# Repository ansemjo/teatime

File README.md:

# Readme

## Notes on the question of voltage regulation

* There's only two components that are somewhat relevant in terms of voltage:
  * the ATtiny; handles 1.7–5.5V per datasheet
  * the LCD; wants 3V per datasheet
* Many of the similar LCD modules are advertised as 3.0–5V compatible.
  * [GoodDisplay's own precautions say that overvoltage will (merely) "shorten its life"](https://www.good-display.com/news/102.html)
  * [Another explainer says that overvoltage usually (only) results in ghosting](https://focuslcds.com/journals/lcd-voltage-inputs-for-lcd-displays-explained/)
* I'll have a diode behind the battery to prevent charging the coin cell in any case.
* The LCD is driven directly by the ATtiny IO pins, so *if* I want to regulate ... I'll need to regulate the input voltage to the ATtiny.
* The ATtiny pins can only handle about VDD + 0.5V, so I'll need either:
  * "Simple" protection with input resistors to limit the current; per § 34.2 of the datasheet it is acceptable to limit the current with $R = \frac{(V_{pin} - (VDD + 0.6))}{I_{Cn}}$, where $I_{Cn} = 1 \text{mA}$
    * How does this interact with the pull-up requirement on I2C pins?
  * "Full" level shifting for any logic pins, i.e. external I2C connectors and programming ports; except UPDI can handle up to 13V regardless of VDD

* Another funky solution would be to omit the regulation and "just" stay within the ATtiny's limits. Then implement the "own voltage" sensing (which is usually used for battery voltage detection; aside: how does that work behind a diode?) to check what voltage is applied on startup. If it's more than 3.3V, use PWM modulation on the IO pins to the display to keep the average at around 3V?

## Driving the LCD

* Aha! These LCDs are so cheap because they don't include and driver electronics. And it's actually not that trivial to drive.
* You *can* apply a constant voltage but that will destroy the LCD over time through ... elctrophoresis? Either way, you need to apply AC by alternating the polarity of each segment during each frame.
* *Do* drive the commons and segments that you *don't* want to be visible, but drive them with equal voltages during both halves of the frame to keep differential at zero. But you still do need to alternate the voltage.
* There's a nice [application note by Atmel: AVR241](https://ww1.microchip.com/downloads/en/AppNotes/doc2569.pdf).
* And [an article by Pacific Display Devices](https://www.pacificdisplay.com/lcd_multiplex_drive.htm).
* And particularly useful is an [application note by ST Microelectronics: AN1447](https://www.st.com/resource/en/application_note/an1447-software-driver-for-4multiplexed-lcd-with-a-standard-st62-stmicroelectronics.pdf). It actually describes how to drive a 4-multiplexed LCD with a simple microcontroller.

## Notes on Components

### The LCD

* Ain't nobody got space for that many pins! I *really* didn't want to use a 40-pin component. Especially because I don't have any microcontrollers that have enough IO ports.
* The 12 pin variant requires time multiplexing but I'm kinda used to that from the other two display projects I built already.

### 32.768 kHz Crystal

* I [picked a crystal from the same series](https://uk.farnell.com/abracon/abs07-120-32-768khz-t/crystal-32-768khz-6pf-3-2-x-1/dp/2467864) that David Johnson-Davies used; but a (to me) more common 12.5 pF loading capacitor value.

* [Per an Electronics StackExchange post](https://electronics.stackexchange.com/questions/39103/selecting-loading-capacitor-values-for-32-khz-crystal), the formula to select (two identical) loading capacitors $C$ is $C_{load} = \frac{C}{2} + C_{parasitic}$, where the parasitic capacitance of the PCB is usually assumed to be around 2.5 pF. Rearranging for the "unknown" yields $C = 2\cdot(C_{load} - C_{parasitic})$ and with $C_{load} = 12.5\,pF$ this gives $C \approx 20\,pF$.
* I chose to use 0603 capacitors because this is a new part in my personal stock, I feel very confident soldering smaller parts than 0805 by now and I'll probably only ever use these capacitors in this exact combination.

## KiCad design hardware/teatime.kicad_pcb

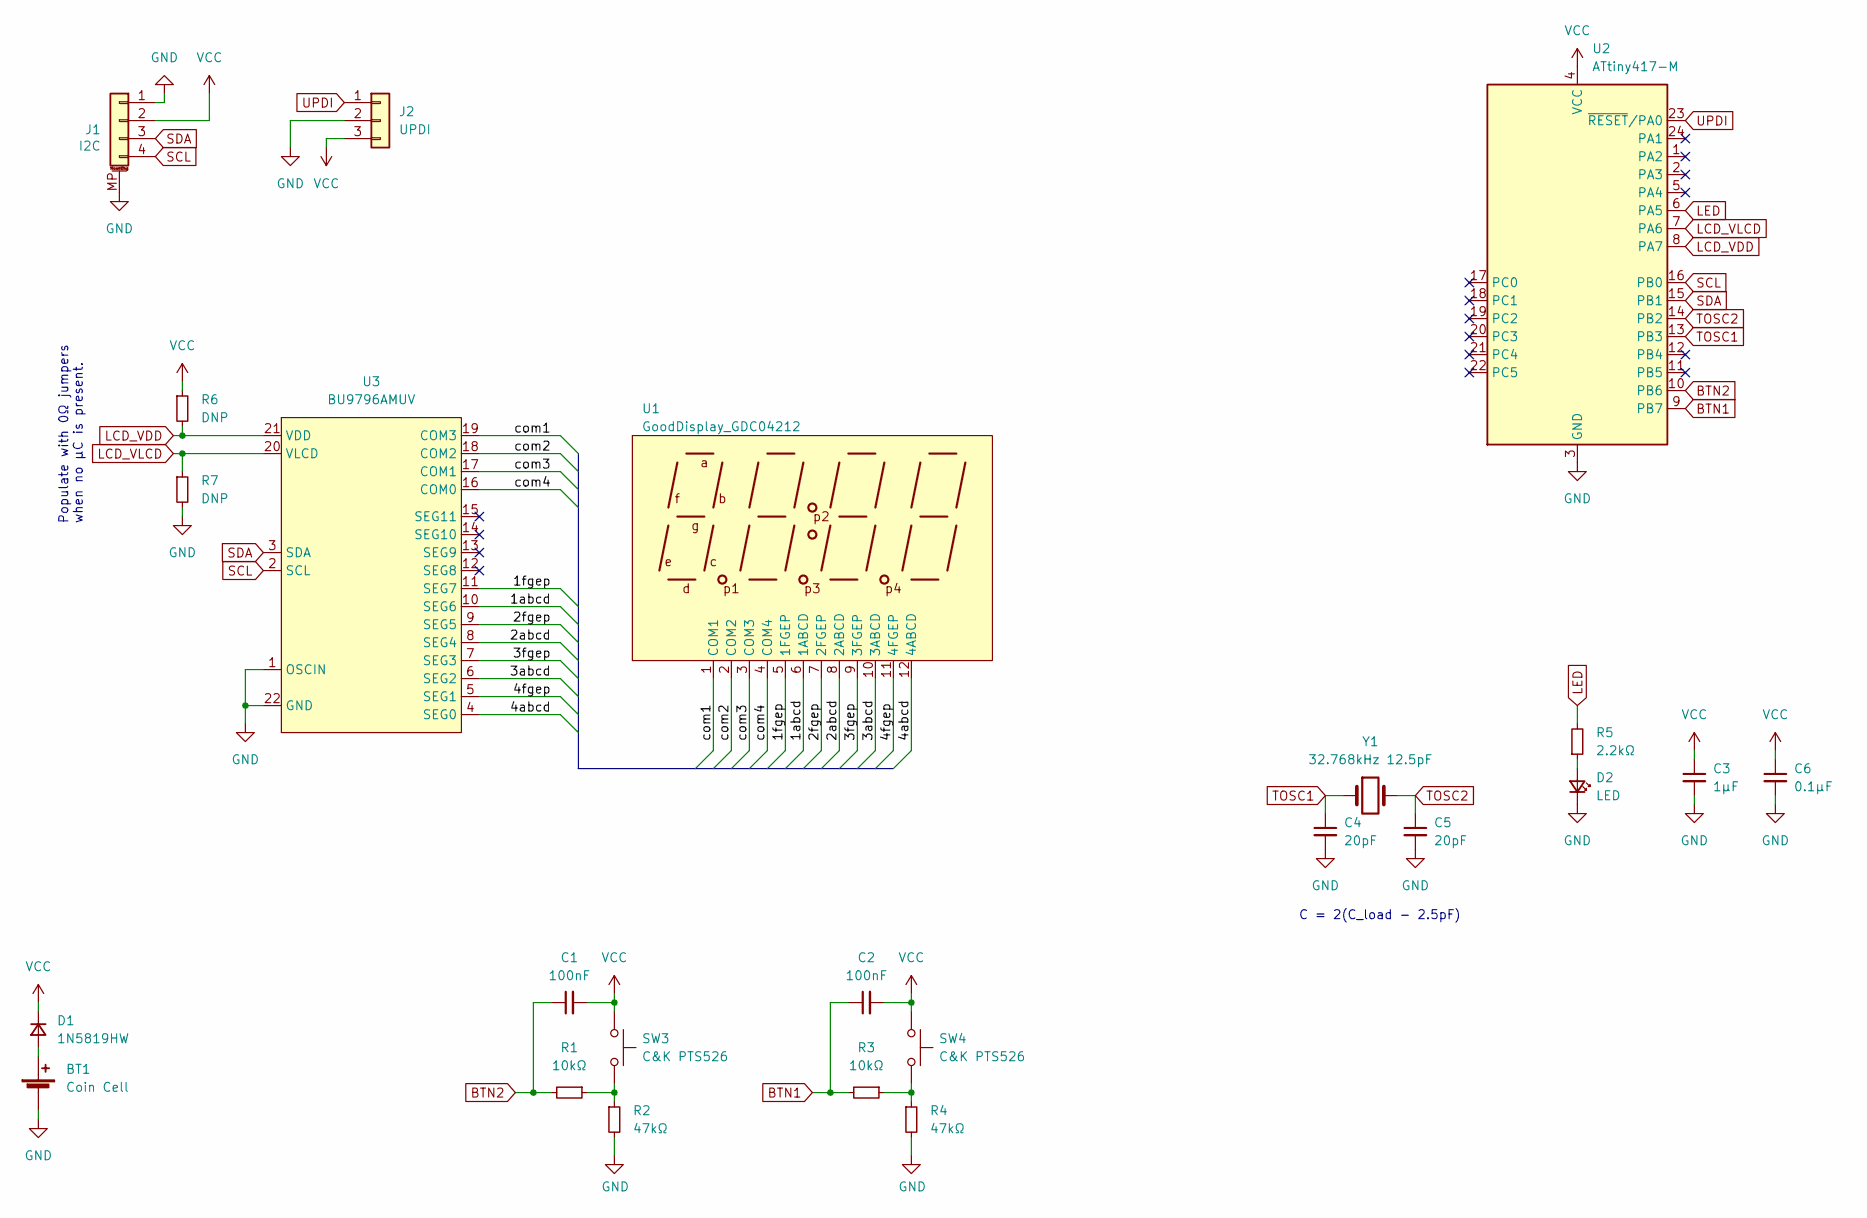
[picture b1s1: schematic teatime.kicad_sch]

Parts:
BT1: Coin Cell; BatteryHolder_Keystone_3034_1x20mm
C1, C2: 100nF; C_0805_2012Metric
C3: 1µF; C_0805_2012Metric
C4, C5: 20pF; C_0603_1608Metric
C6: 0.1µF; C_0805_2012Metric
D1: 1N5819HW; D_SOD-123
D2: LED; LED_0805_2012Metric
J1: I2C; JST_SH_SM04B-SRSS-TB_1x04-1MP_P1.00mm_Horizontal
J2: UPDI; UPDI_PogoProg
R1, R3: 10kΩ; R_0805_2012Metric
R2, R4: 47kΩ; R_0805_2012Metric
R5: 2.2kΩ; R_0805_2012Metric
R6, R7: DNP; R_0805_2012Metric
SW3, SW4: C&K PTS526; SW_SPST_SKQG_WithStem
U1: GoodDisplay_GDC04212; LCD-12PIN
U2: ATtiny417-M; QFN-24-1EP_4x4mm_P0.5mm_EP2.6x2.6mm
U3: BU9796AMUV; VQFN-24-1EP_4x4mm_P0.5mm_EP2.45x2.45mm
Y1: 32.768kHz 12.5pF; Crystal_SMD_3215-2Pin_3.2x1.5mm

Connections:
/1abcd: U1.6 (1ABCD), U3.10 (SEG6)
/1fgep: U1.5 (1FGEP), U3.11 (SEG7)
/2abcd: U1.8 (2ABCD), U3.8 (SEG4)
/2fgep: U1.7 (2FGEP), U3.9 (SEG5)
/3abcd: U1.10 (3ABCD), U3.6 (SEG2)
/3fgep: U1.9 (3FGEP), U3.7 (SEG3)
/4abcd: U1.12 (4ABCD), U3.4 (SEG0)
/4fgep: U1.11 (4FGEP), U3.5 (SEG1)
/com1: U1.1 (COM1), U3.19 (COM3)
/com2: U1.2 (COM2), U3.18 (COM2)
/com3: U1.3 (COM3), U3.17 (COM1)
/com4: U1.4 (COM4), U3.16 (COM0)
BTN1: C2.1, R3.2, U2.9 (PB7)
BTN2: C1.1, R1.2, U2.10 (PB6)
GND: BT1.2 (-), C3.2, C4.2, C5.2, C6.2, D2.1 (K), J1.1, J1.MP (MountPin), J2.2, R2.2, R4.2, R7.2, U2.3 (GND), U2.25 (GND), U3.1 (OSCIN), U3.22 (GND), U3.23 (TEST1), U3.24 (TEST2), U3.25 (EXT-PAD)
LCD_VDD: R6.2, U2.8 (PA7), U3.21 (VDD)
LCD_VLCD: R7.1, U2.7 (PA6), U3.20 (VLCD)
LED: R5.2, U2.6 (PA5)
unnamed: BT1.1 (+), D1.2 (A)
unnamed: D2.2 (A), R5.1
unnamed: R1.1, R2.1, SW3.2
unnamed: R3.1, R4.1, SW4.2
SCL: J1.4, U2.16 (PB0), U3.2 (SCL)
SDA: J1.3, U2.15 (PB1), U3.3 (SDA)
TOSC1: C4.1, U2.13 (PB3), Y1.1
TOSC2: C5.1, U2.14 (PB2), Y1.2
UPDI: J2.1, U2.23 (~RESET/PA0)
VCC: C1.2, C2.2, C3.1, C6.1, D1.1 (K), J1.2, J2.3, R6.1, SW3.1, SW4.1, U2.4 (VCC)

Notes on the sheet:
Populate with 0Ω jumpers when no µC is present.
C = 2(C_load - 2.5pF)

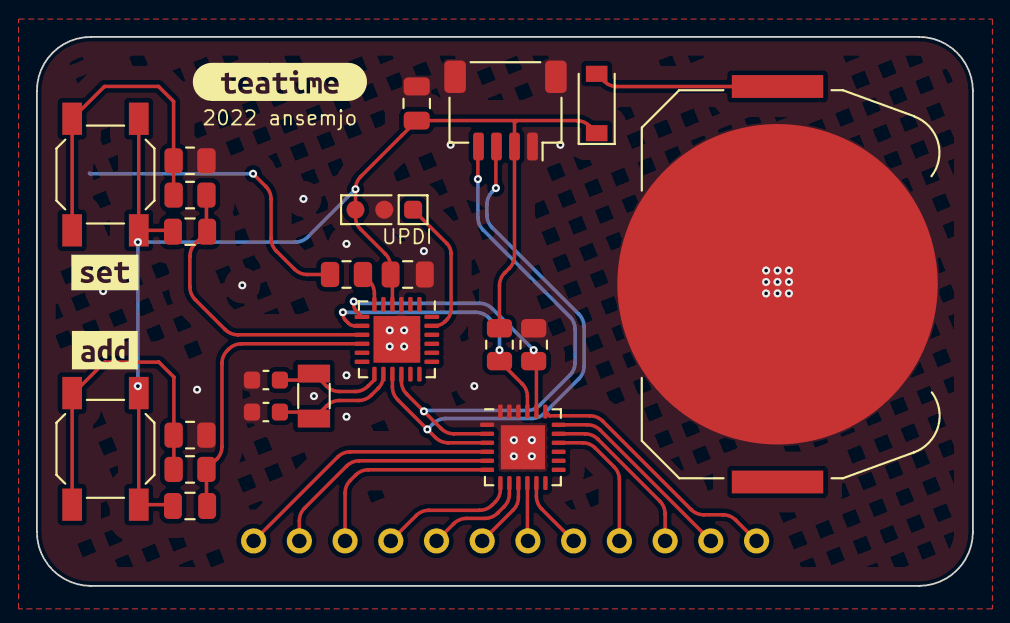
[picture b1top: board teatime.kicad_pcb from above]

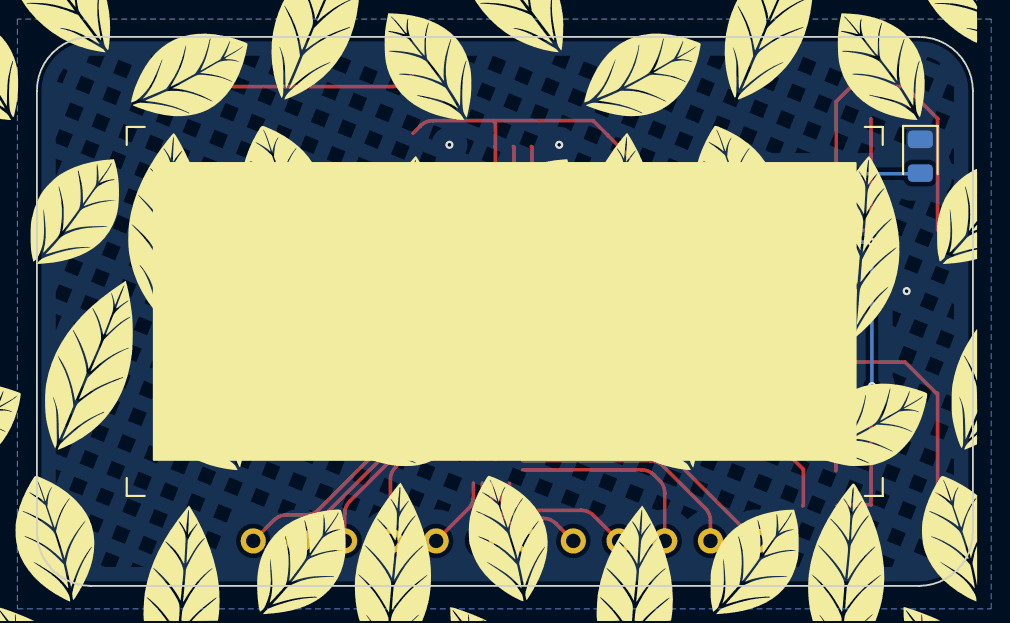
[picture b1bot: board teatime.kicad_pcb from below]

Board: 2 copper layers, 52.0 x 30.5 mm, 27 parts (2 on the bottom side), 28 nets.

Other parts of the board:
kibuzzard-6305512F: G***; kibuzzard-6305512F
kibuzzard-63055090: G***; kibuzzard-63055090
kibuzzard-63055120: G***; kibuzzard-63055120

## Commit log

2022-08-25 first teatime version without dedicated display controller
2022-08-25 updated design using dedicated rohm BU9796AMUV driver
2022-08-25 rounded tracks
2022-09-29 add link to lcd driver datasheet in schematic
2022-09-29 generate interactive bom for soldering
2022-09-29 move hardware files into subdirectory
2022-09-30 initialize firmware dir with platformio project
    configure system clocks and crystal and only use PIT to blink the LED,
    otherwise just go to sleep
2022-10-04 add two images and lcd controller datasheet
2022-10-04 add lcd driver and segment mapping headers
    also switch down to 10 mhz cpu clock due to safe operating area at 3V
    coin cell battery voltage
2022-10-05 implement i2c_controller to write digits to display
    it is using an interrupt-driven style to be able to save power in idle
    mode while waiting for the next packet
2022-10-06 move some setup code around, split in separate files
2022-10-06 test button filtering with pin interrupts
2022-10-06 restore previous sleep mode in i2c controller
2022-10-06 [WIP] implement an actual timer function
    this is a bit of spaghetti code but it works like I intended my teatimer
